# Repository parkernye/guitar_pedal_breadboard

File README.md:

# guitar_pedal_breadboard
Prototype Board for Guitar Pedals

I wanted a simple PCB that I could place two breadboards on to help prototype my guitar pedals. 
It features multiple supply voltages, an input and output jack, and spots to plug in potentiometers of different values. 
Inspiration taken from the PedalPCB protoboard.

Future Modifications
- Swap DC jack polarity to match guitar pedal standards
- Add 'stereo' capabilities

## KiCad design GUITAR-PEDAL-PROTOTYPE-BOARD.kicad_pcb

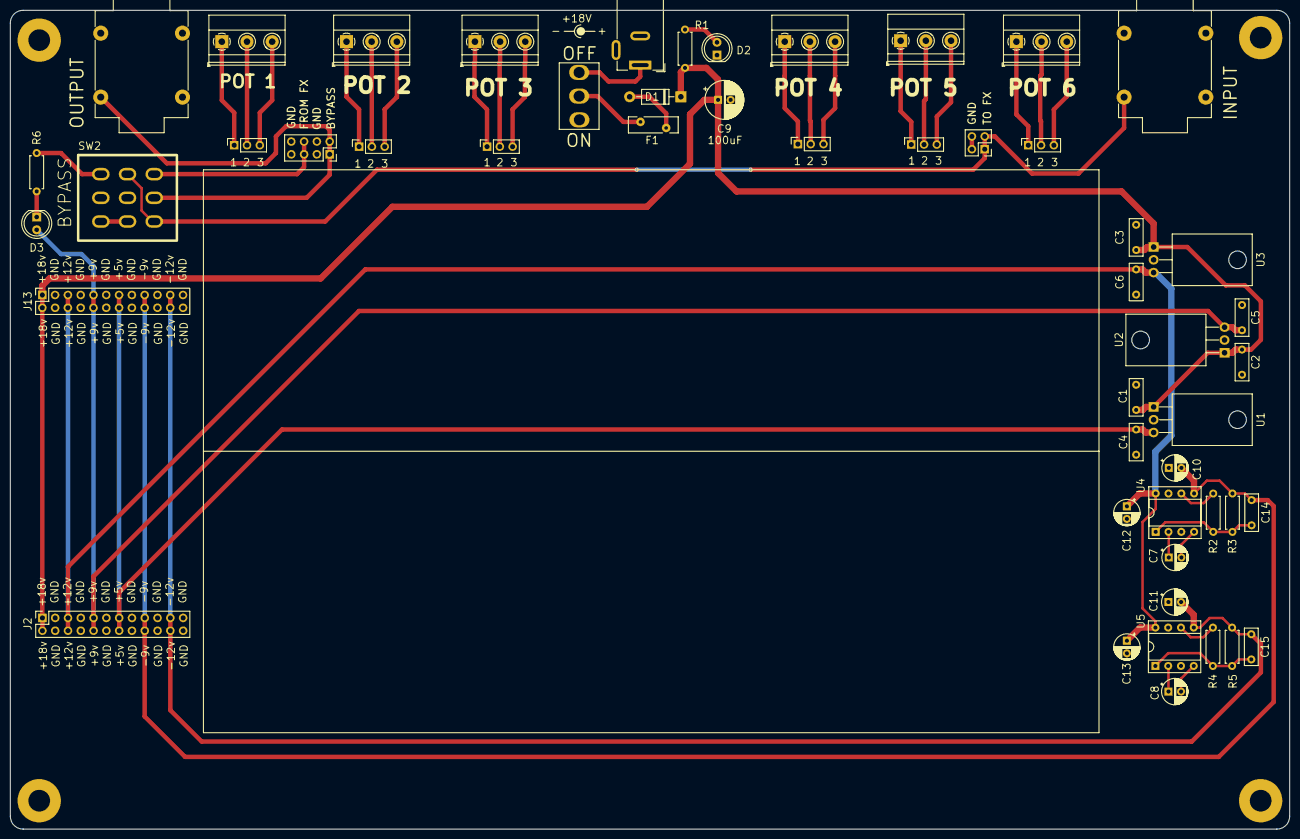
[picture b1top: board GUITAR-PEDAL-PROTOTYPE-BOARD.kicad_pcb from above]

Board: 2 copper layers, 254.0 x 162.6 mm, 51 parts (0 on the bottom side), 43 nets.

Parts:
C1, C2, C3: .33uF; C_Rect_L7.2mm_W2.5mm_P5.00mm_FKS2_FKP2_MKS2_MKP2
C4, C5, C6, C14, C15: .1uF; C_Rect_L7.2mm_W2.5mm_P5.00mm_FKS2_FKP2_MKS2_MKP2
C7, C8: 10uF; CP_Radial_D5.0mm_P2.50mm
C9: 100uF; CP_Radial_D7.5mm_P2.50mm
C10, C11, C12, C13: 2.2uF; CP_Radial_D5.0mm_P2.50mm
D1: 1N5817; D_DO-41_SOD81_P10.16mm_Horizontal
D2, D3: LED; LED_D5.0mm
F1: Polyfuse; Fuse_Bourns_MF-RHT100
J1: Barrel_Jack_Switch; BarrelJack_Wuerth_6941xx301002
J2, J13: Conn_02x12_Odd_Even; PinSocket_2x12_P2.54mm_Vertical
J3, J5: AudioJack2_Dual_Switch; Jack_6.35mm_Neutrik_NMJ4HFD2_Horizontal
J4: Conn_02x02_Odd_Even; PinSocket_2x02_P2.54mm_Vertical
J6: Conn_02x04_Odd_Even; PinSocket_2x04_P2.54mm_Vertical
J7, J8, J9, J10, J11, J12: Conn_01x03; TerminalBlock_Phoenix_MKDS-1,5-3_1x03_P5.00mm_Horizontal
J15, J16, J17, J18, J19, J20: Conn_01x03; PinSocket_1x03_P2.54mm_Vertical
R1, R6: 4k7; R_Axial_DIN0207_L6.3mm_D2.5mm_P7.62mm_Horizontal
R2, R4: 20k; R_Axial_DIN0207_L6.3mm_D2.5mm_P7.62mm_Horizontal
R3: 180k; R_Axial_DIN0207_L6.3mm_D2.5mm_P7.62mm_Horizontal
R5: 220k; R_Axial_DIN0207_L6.3mm_D2.5mm_P7.62mm_Horizontal
SW1: SW_SPST; THT-SWITCH-SPST
SW2: SW_Stomp_3PDT_Tayda
U1: L7805; TO-220-3_Horizontal_TabDown
U2: L7809; TO-220-3_Horizontal_TabDown
U3: L7812; TO-220-3_Horizontal_TabDown
U4, U5: LT1054; DIP-8_W7.62mm_Socket

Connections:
+4V: C1.1, C2.1, C3.1, C9.1, D1.1 (K), J2.1, J2.2, J13.1, J13.2, R1.1, U1.1 (IN), U2.1 (IN), U3.1 (IN)
+5V: C4.1, J2.13, J2.14, J13.13, J13.14, U1.3 (OUT)
+9V: C5.1, D3.2 (A), J2.9, J2.10, J13.9, J13.10, U2.3 (OUT)
+12V: C6.1, C12.1, C13.1, J2.5, J2.6, J13.5, J13.6, U3.3 (OUT), U4.8 (V+), U5.8 (V+)
-9V: C10.2, C14.1, J2.17, J2.18, J13.17, J13.18, R3.1, U4.5 (-VOUT)
-12V: C11.2, C15.1, J2.21, J2.22, J13.21, J13.22, R5.1, U5.5 (-VOUT)
BREADBOARD_OUT: J6.5, J6.6, SW2.7 (A)
INPUT_SLEEVE: C1.2, C2.2, C3.2, C4.2, C5.2, C6.2, C9.2, C10.1, C11.1, C12.2, C13.2, D2.1 (K), J1.2, J1.3, J2.3, J2.4, J2.7, J2.8, J2.11, J2.12, J2.15, J2.16, J2.19, J2.20, J2.23, J2.24, J3.S, J4.3, J4.4, J5.S, J6.3, J6.4, J6.7, J6.8, J13.3, J13.4, J13.7, J13.8, J13.11, J13.12, J13.15, J13.16, J13.19, J13.20, J13.23, J13.24, SW2.2 (B), U1.2 (GND), U2.2 (GND), U3.2 (GND), U4.3 (GND), U5.3 (GND)
INPUT_TIP: J3.T, J4.1, J4.2, SW2.4 (A), SW2.9 (C)
unnamed: C7.1, U4.2 (CAP+)
unnamed: C7.2, U4.4 (CAP-)
unnamed: C8.1, U5.2 (CAP+)
unnamed: C8.2, U5.4 (CAP-)
unnamed: C14.2, R2.2, R3.2, U4.1 (FB/SHDN)
unnamed: C15.2, R4.2, R5.2, U5.1 (FB/SHDN)
unnamed: D1.2 (A), F1.2
unnamed: D2.2 (A), R1.2
unnamed: D3.1 (K), R6.2
unnamed: F1.1, SW1.2 (B)
unnamed: J1.1, SW1.1 (A)
unnamed: J10.1, J18.1
unnamed: J10.2, J18.2
unnamed: J10.3, J18.3
unnamed: J11.1, J19.1
unnamed: J11.2, J19.2
unnamed: J11.3, J19.3
unnamed: J12.1, J20.1
unnamed: J12.2, J20.2
unnamed: J12.3, J20.3
unnamed: J7.1, J15.1
unnamed: J7.2, J15.2
unnamed: J7.3, J15.3
unnamed: J8.1, J16.1
unnamed: J8.2, J16.2
unnamed: J8.3, J16.3
unnamed: J9.1, J17.1
unnamed: J9.2, J17.2
unnamed: J9.3, J17.3
unnamed: R2.1, U4.6 (VREF)
unnamed: R4.1, U5.6 (VREF)
unnamed: R6.1, SW2.1 (A)
unnamed: SW2.3 (C), SW2.6 (C)
OUTPUT_TIP: J5.T, J6.1, J6.2, SW2.8 (B)
